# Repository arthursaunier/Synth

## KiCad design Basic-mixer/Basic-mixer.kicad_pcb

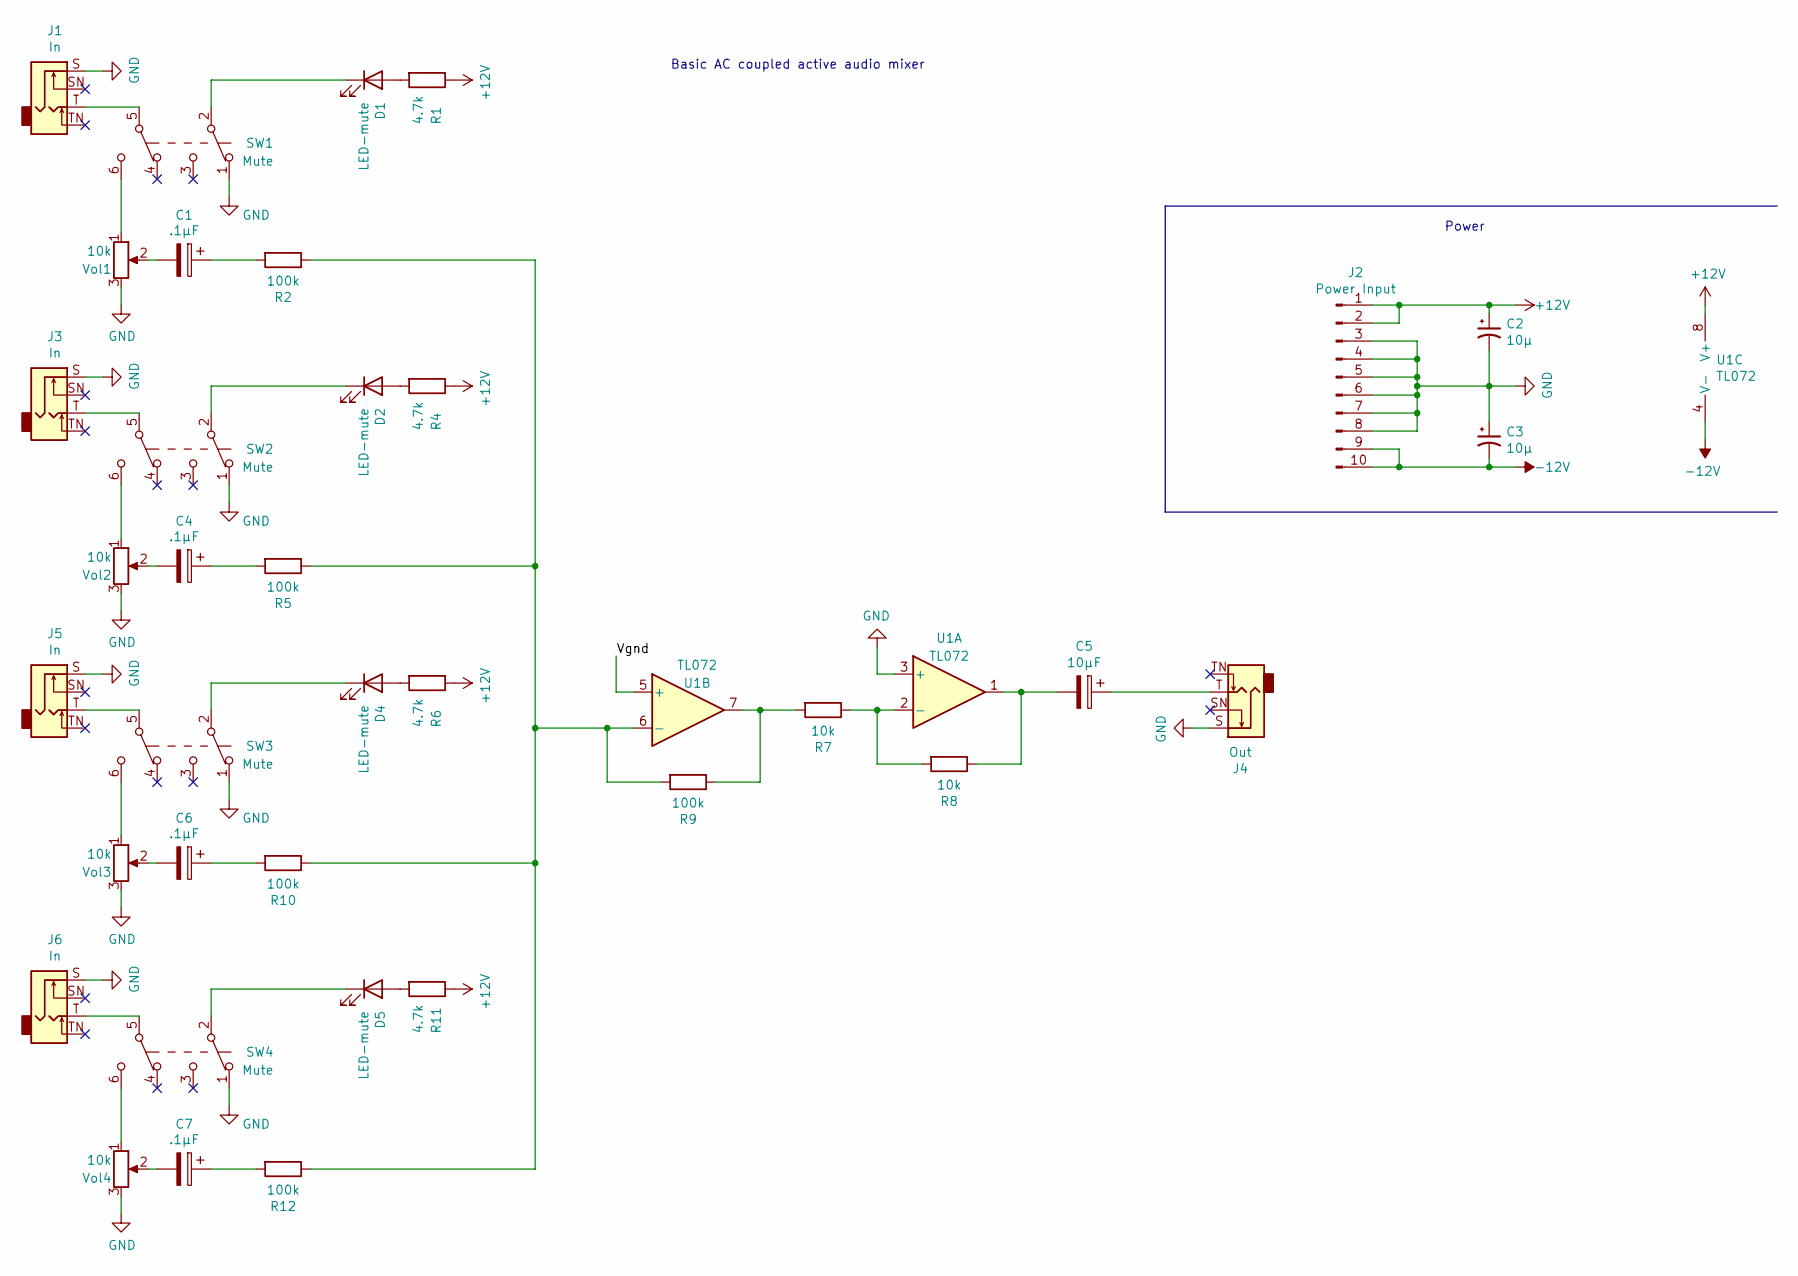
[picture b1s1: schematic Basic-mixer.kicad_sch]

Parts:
C1, C4, C6, C7: .1µF; CP_Radial_D5.0mm_P2.00mm
C2, C3: 10µ; CP_Radial_D5.0mm_P2.00mm
C5: 10µF; CP_Radial_D5.0mm_P2.00mm
D1, D2, D4, D5: LED-mute; LED_D4.0mm
J1, J3, J5, J6: In; Thonkiconn
J2: Power Input; PinHeader_2x05_P2.54mm_Vertical
J4: Out; Thonkiconn
R1, R4, R6, R11: 4.7k; R_Axial_DIN0207_L6.3mm_D2.5mm_P10.16mm_Horizontal
R2, R5, R9, R10, R12: 100k; R_Axial_DIN0207_L6.3mm_D2.5mm_P10.16mm_Horizontal
R7, R8: 10k; R_Axial_DIN0207_L6.3mm_D2.5mm_P10.16mm_Horizontal
SW1, SW2, SW3, SW4: Mute; SW_DPDT_Toggle
U1: TL072; DIP-8_W7.62mm_Socket
Vol1, Vol2, Vol3, Vol4: 10k; Pot-bourns-alpha

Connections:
+12V: C2.1, J2.1, J2.2, R1.1, R4.1, R6.1, R11.1, U1.8 (V+)
-12V: C3.2, J2.9, J2.10, U1.4 (V-)
/Vgnd: U1.5 (+)
GND: C2.2, C3.1, J1.S, J2.3, J2.4, J2.5, J2.6, J2.7, J2.8, J3.S, J4.S, J5.S, J6.S, SW1.1 (A), SW2.1 (A), SW3.1 (A), SW4.1 (A), U1.3 (+), Vol1.3, Vol2.3, Vol3.3, Vol4.3
unnamed: C1.1, R2.2
unnamed: C1.2, Vol1.2
unnamed: C4.1, R5.2
unnamed: C4.2, Vol2.2
unnamed: C5.1, J4.T
unnamed: C5.2, R8.1, U1.1
unnamed: C6.1, R10.2
unnamed: C6.2, Vol3.2
unnamed: C7.1, R12.2
unnamed: C7.2, Vol4.2
unnamed: D1.1 (K), SW1.2 (B)
unnamed: D1.2 (A), R1.2
unnamed: D2.1 (K), SW2.2 (B)
unnamed: D2.2 (A), R4.2
unnamed: D4.1 (K), SW3.2 (B)
unnamed: D4.2 (A), R6.2
unnamed: D5.1 (K), SW4.2 (B)
unnamed: D5.2 (A), R11.2
unnamed: J1.T, SW1.5 (B)
unnamed: J3.T, SW2.5 (B)
unnamed: J5.T, SW3.5 (B)
unnamed: J6.T, SW4.5 (B)
unnamed: R7.1, R8.2, U1.2 (-)
unnamed: R7.2, R9.1, U1.7
unnamed: R2.1, R5.1, R9.2, R10.1, R12.1, U1.6 (-)
unnamed: SW1.6 (C), Vol1.1
unnamed: SW2.6 (C), Vol2.1
unnamed: SW3.6 (C), Vol3.1
unnamed: SW4.6 (C), Vol4.1

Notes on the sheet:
Power
Basic AC coupled active audio mixer

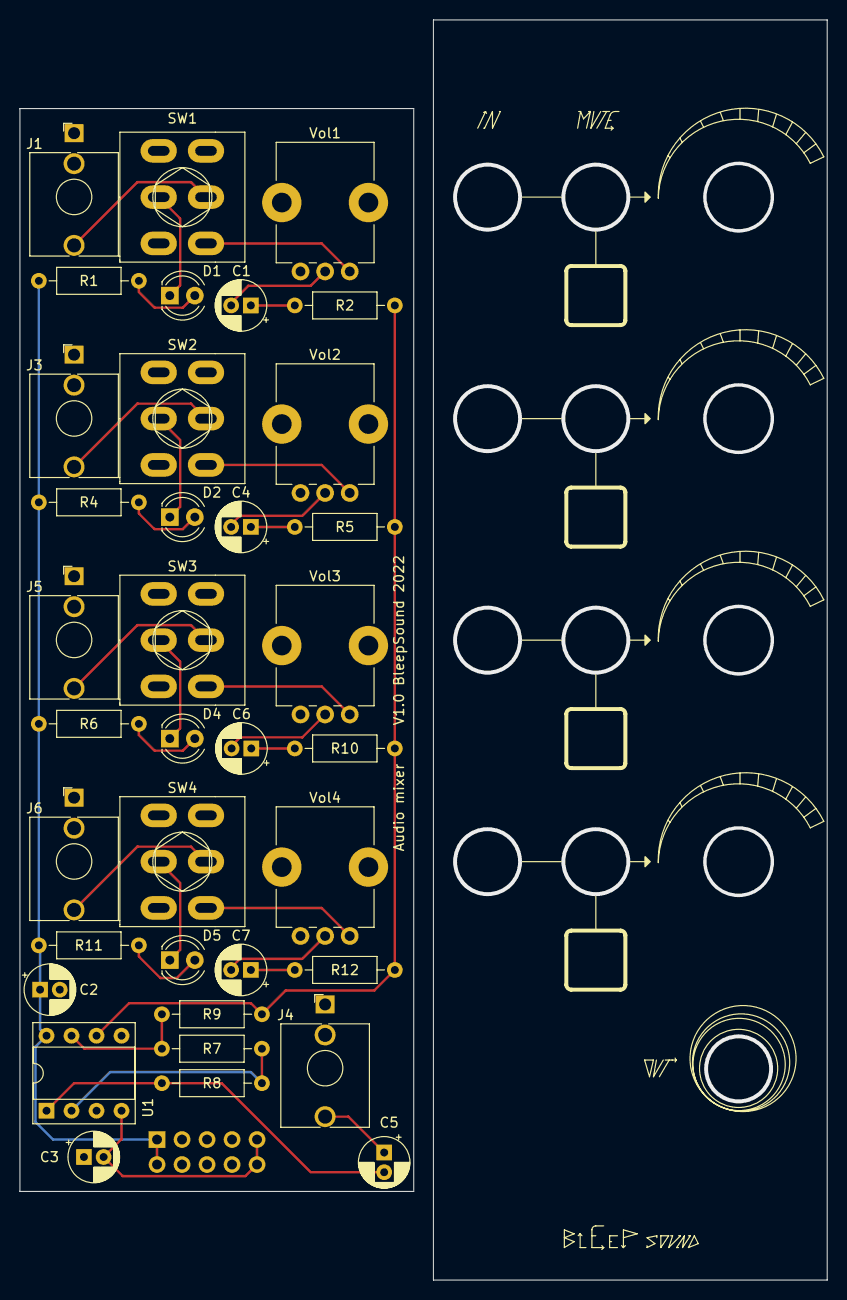
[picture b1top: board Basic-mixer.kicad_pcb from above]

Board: 2 copper layers, 82.0 x 128.0 mm, 37 parts (1 on the bottom side), 32 nets.

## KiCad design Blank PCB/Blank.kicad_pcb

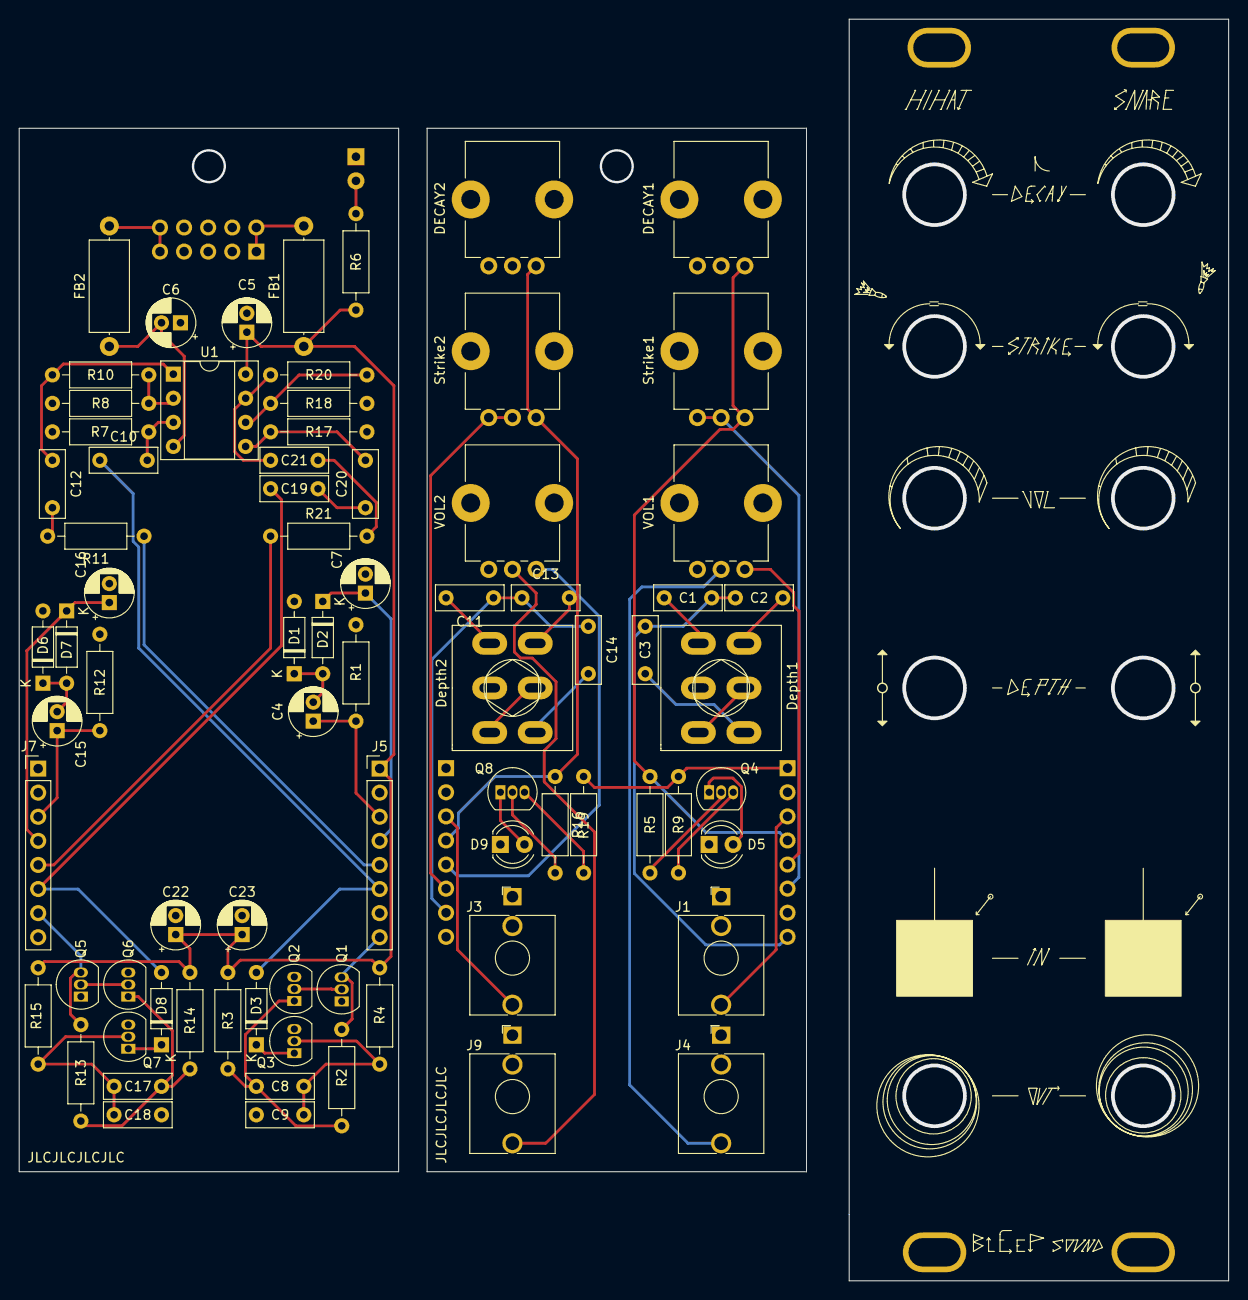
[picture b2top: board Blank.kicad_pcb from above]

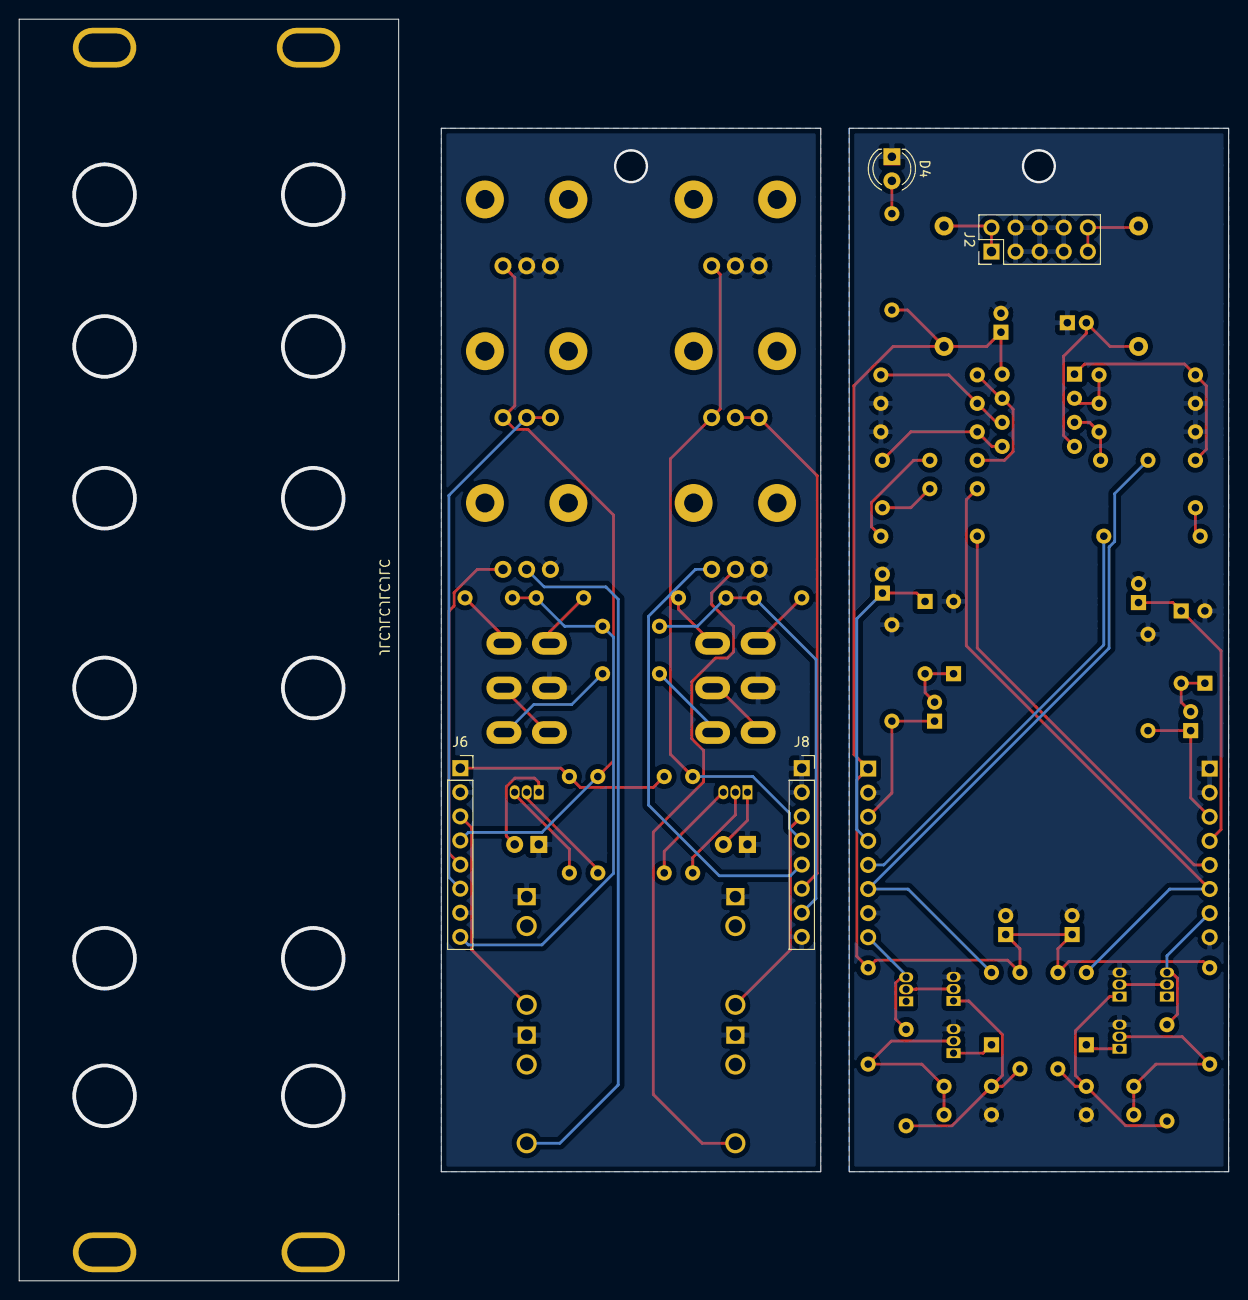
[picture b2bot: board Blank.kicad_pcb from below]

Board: 2 copper layers, 127.5 x 133.0 mm, 81 parts (4 on the bottom side), 51 nets.

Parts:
C1, C11, C12, C21: 10µF; C_Disc_D7.0mm_W2.5mm_P5.00mm
C2, C8, C13, C17: 1µF; C_Disc_D7.0mm_W2.5mm_P5.00mm
C3, C9, C14: 0.1µF; C_Disc_D7.0mm_W2.5mm_P5.00mm
C4, C7, C15, C16: 10µF; CP_Radial_D5.0mm_P2.00mm
C5, C6: 10µ; CP_Radial_D5.0mm_P2.00mm
C10, C20: .1µF; C_Disc_D7.0mm_W2.5mm_P5.00mm
C18: 10nF; C_Disc_D7.0mm_W2.5mm_P5.00mm
C19: 680pF; C_Disc_D7.0mm_W2.5mm_P5.00mm
C22, C23: 100µ; CP_Radial_D5.0mm_P2.00mm
D1, D2, D3, D6, D7, D8: 1N4148; D_DO-35_SOD27_P7.62mm_Horizontal
D4: LED-12V; LED_D4.0mm
D5: Trig Snare; LED_D4.0mm
D9: Trig_HiHat; LED_D4.0mm
DECAY1, DECAY2: 100k; Potentiometer_Bourns_PTV09A-1_Single_Vertical
Depth1, Depth2: SW_Push_DPDT; SW_DPDT_Toggle
FB1, FB2: 10R; L_Axial_L9.5mm_D4.0mm_P12.70mm_Horizontal_Fastron_SMCC
J1: Snare IN; Jack_3.5mm_QingPu_WQP-PJ398SM_Vertical_CircularHoles
J2: Power Input; PinHeader_2x05_P2.54mm_Vertical
J3: HiHat IN; Jack_3.5mm_QingPu_WQP-PJ398SM_Vertical_CircularHoles
J4: Snare OUT; Jack_3.5mm_QingPu_WQP-PJ398SM_Vertical_CircularHoles
J5, J7: Conn_01x08_Male; PinHeader_1x08_P2.54mm_Vertical
J6, J8: Conn_01x08_Female; PinSocket_1x08_P2.54mm_Vertical
J9: HiHat OUT; Jack_3.5mm_QingPu_WQP-PJ398SM_Vertical_CircularHoles
Q1, Q2, Q3, Q5, Q6, Q7: BC546; TO-92_Inline
Q4, Q8: 2N3904; TO-92_Inline
R1, R3, R12, R14: 4k7; R_Axial_DIN0207_L6.3mm_D2.5mm_P10.16mm_Horizontal
R2, R13: 47k; R_Axial_DIN0207_L6.3mm_D2.5mm_P10.16mm_Horizontal
R4, R7, R11, R15, R17, R21: 1M; R_Axial_DIN0207_L6.3mm_D2.5mm_P10.16mm_Horizontal
R5, R10, R16, R20: 100k; R_Axial_DIN0207_L6.3mm_D2.5mm_P10.16mm_Horizontal
R6: 2.2k; R_Axial_DIN0207_L6.3mm_D2.5mm_P10.16mm_Horizontal
R8, R18: 6.8k; R_Axial_DIN0207_L6.3mm_D2.5mm_P10.16mm_Horizontal
R9, R19: 1k; R_Axial_DIN0207_L6.3mm_D2.5mm_P10.16mm_Horizontal
Strike1, Strike2: 100k; Potentiometer_Bourns_PTV09A-1_Single_Vertical
U1: TL072; DIP-8_W7.62mm_Socket
VOL1, VOL2: 10k; Potentiometer_Bourns_PTV09A-1_Single_Vertical

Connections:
+12V: C5.1, C22.1, C23.1, FB1.1, J5.1, J6.1, R3.1, R4.1, R6.1, R9.1, R14.1, R15.1, R19.1, U1.8
-12V: C6.2, FB2.1, U1.4
/DeH: C1.1, C2.1, C3.1, J5.8, J6.8, Q1.3, R2.1
/HiDH: C11.1, C13.1, C14.1, J7.7, J8.7, Q5.3, R13.1
/HiH: C16.1, D7.1, DECAY2.1, J7.4, J8.4, R16.1, Strike2.1
/HiI: C15.1, J3.T, J7.3, J8.3, R12.1
/HiO: J7.5, J8.5, R21.1, VOL2.1
/Ho: C19.1, D8.2, J7.6, J8.6, Strike2.2, Strike2.3
/SnH: C7.1, D2.1, DECAY1.1, J5.4, J6.4, R5.1, Strike1.1
/SnI: C4.1, J1.T, J5.3, J6.3, R1.1
/SnO: J5.5, J6.5, R11.1, VOL1.1
/So: C10.1, D3.2, J5.6, J6.6, Strike1.2, Strike1.3
GND: C5.2, C6.1, C7.2, C9.1, C16.2, C18.1, C22.2, C23.2, D1.2, D4.1, D5.1, D6.2, D9.1, DECAY1.2, DECAY1.3, DECAY2.2, DECAY2.3, Depth1.2, Depth2.2, J1.S, J2.3, J2.4, J2.5, J2.6, J2.7, J2.8, J3.S, J4.S, J5.2, J5.7, J6.2, J6.7, J7.1, J7.2, J7.8, J8.1, J8.2, J8.8, J9.S, Q2.3, Q3.3, Q6.3, Q7.3, R1.2, R7.2, R8.2, R12.2, R17.2, R18.2, VOL1.3, VOL2.3
unnamed: C1.2, Depth1.1
unnamed: C2.2, Depth1.4
unnamed: C3.2, Depth1.6
unnamed: C4.2, D1.1, D2.2
unnamed: C8.1, Q2.1, R2.2, R3.2
unnamed: C8.2, C9.2, Q3.2, R4.2
unnamed: C10.2, R7.1, U1.3
unnamed: C11.2, Depth2.1
unnamed: C12.1, R10.1, U1.1
unnamed: C12.2, R11.2
unnamed: C13.2, Depth2.4
unnamed: C14.2, Depth2.6
unnamed: C15.2, D6.1, D7.2
unnamed: C17.1, Q6.1, R13.2, R14.2
unnamed: C17.2, C18.2, Q7.2, R15.2
unnamed: C19.2, C20.1
unnamed: C20.2, R17.1, U1.5
unnamed: C21.1, R20.1, U1.7
unnamed: C21.2, R21.2
unnamed: D3.1, Q3.1
unnamed: D4.2, R6.2
unnamed: D5.2, Q4.1
unnamed: D8.1, Q7.1
unnamed: D9.2, Q8.1
unnamed: Depth1.3, Depth1.5
unnamed: Depth2.3, Depth2.5
unnamed: FB1.2, J2.1, J2.2
unnamed: FB2.2, J2.9, J2.10
unnamed: J4.T, VOL1.2
unnamed: J9.T, VOL2.2
unnamed: Q1.2, Q2.2
unnamed: Q4.2, R5.2
unnamed: Q4.3, R9.2
unnamed: Q5.2, Q6.2
unnamed: Q8.2, R16.2
unnamed: Q8.3, R19.2
unnamed: R8.1, R10.2, U1.2
unnamed: R18.1, R20.2, U1.6

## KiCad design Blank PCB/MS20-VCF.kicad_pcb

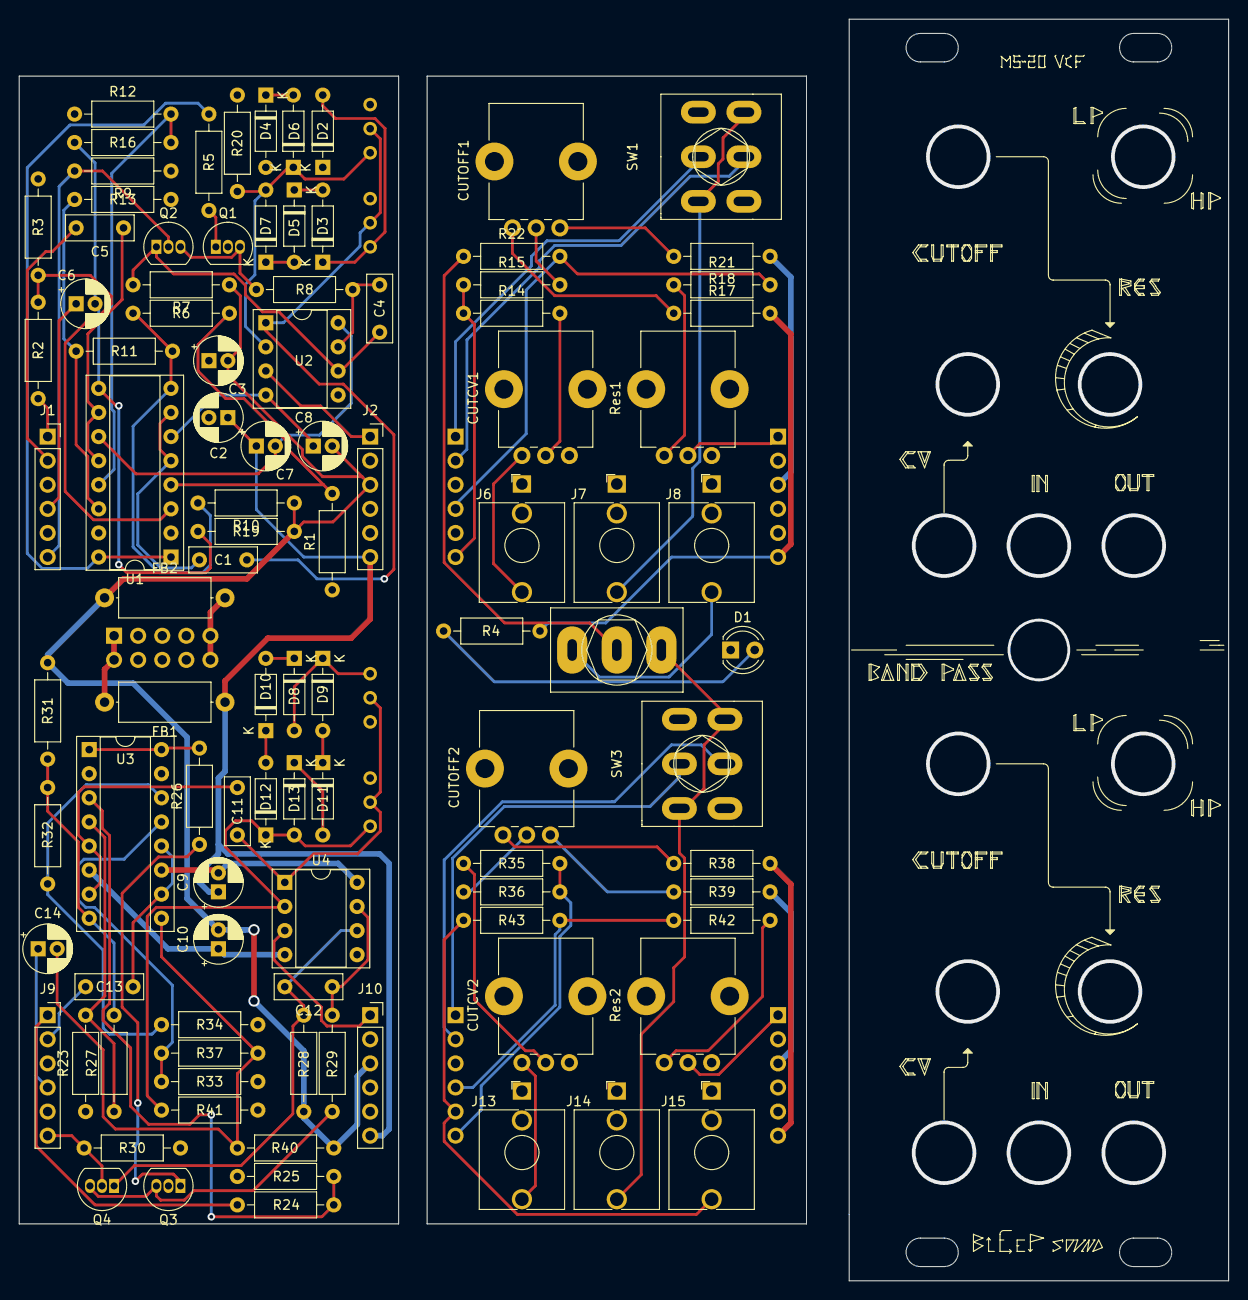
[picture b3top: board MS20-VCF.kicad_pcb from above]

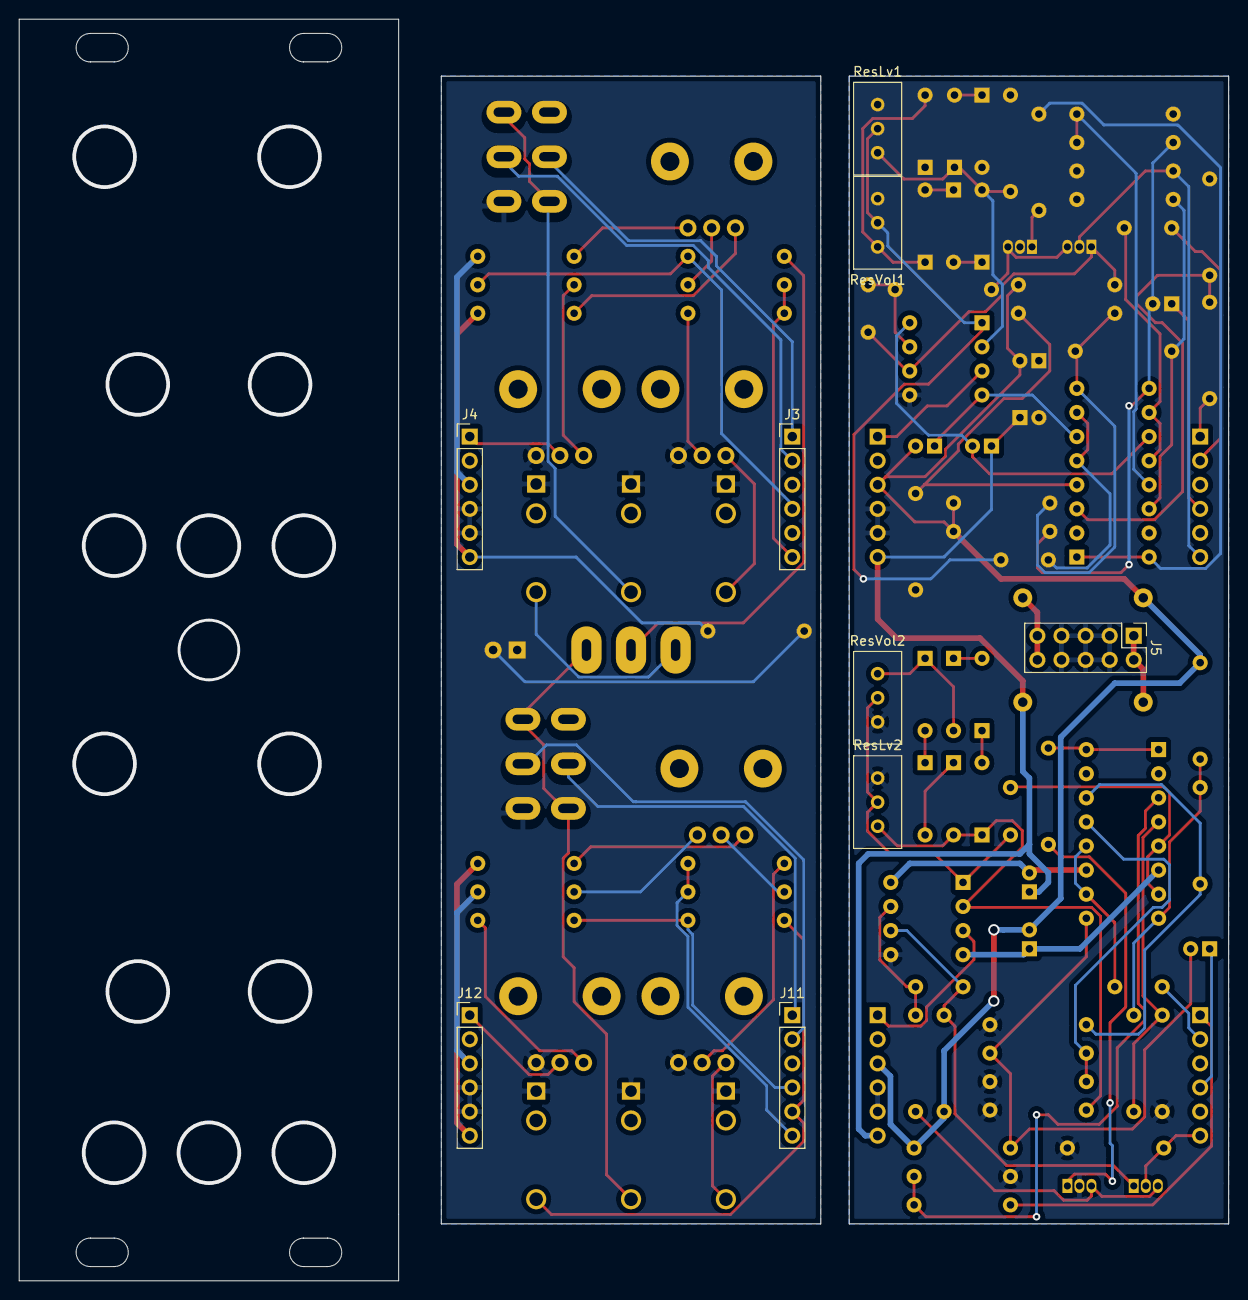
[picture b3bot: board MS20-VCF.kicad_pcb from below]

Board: 2 copper layers, 127.5 x 133.0 mm, 108 parts (9 on the bottom side), 77 nets.

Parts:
C1, C4, C5, C11, C12, C13: 1nF; C_Disc_D7.0mm_W2.5mm_P5.00mm
C2, C3: 10µ; CP_Radial_D5.0mm_P2.00mm
C6, C14: 10µF; CP_Radial_D5.0mm_P2.00mm
C7, C8, C9, C10: 0.1µ; CP_Radial_D5.0mm_P2.00mm
CUTCV1, CUTCV2: 100k; Potentiometer_Bourns_PTV09A-1_Single_Vertical
CUTOFF1, CUTOFF2: 100k; Potentiometer_Bourns_PTV09A-1_Single_Vertical
D1: LED-12V; LED_D4.0mm
D2, D3, D4, D5, D6, D7, D8, D9, D10, D11, D12, D13: 1N4148; D_DO-35_SOD27_P7.62mm_Horizontal
FB1, FB2: 10R; L_Axial_L9.5mm_D4.0mm_P12.70mm_Horizontal_Fastron_SMCC
J1, J2, J9, J10: Conn_CircuitBoard; PinSocket_1x06_P2.54mm_Vertical
J3, J4, J11, J12: Conn_JackBoard; PinHeader_1x06_P2.54mm_Vertical
J5: Power Input; PinHeader_2x05_P2.54mm_Vertical
J6: FilterCV1; Jack_3.5mm_QingPu_WQP-PJ398SM_Vertical_CircularHoles
J7: FilterIn1; Jack_3.5mm_QingPu_WQP-PJ398SM_Vertical_CircularHoles
J8: FilterOut1; Jack_3.5mm_QingPu_WQP-PJ398SM_Vertical_CircularHoles
J13: FilterCV2; Jack_3.5mm_QingPu_WQP-PJ398SM_Vertical_CircularHoles
J14: FilterIn2; Jack_3.5mm_QingPu_WQP-PJ398SM_Vertical_CircularHoles
J15: FilterOut2; Jack_3.5mm_QingPu_WQP-PJ398SM_Vertical_CircularHoles
Q1, Q2, Q3, Q4: BC559; TO-92_Inline
R1, R3, R12, R13, R23, R25, R33, R34: 470; R_Axial_DIN0207_L6.3mm_D2.5mm_P10.16mm_Horizontal
R2, R6, R7, R11, R15, R16, R24, R27, R28, R32, R36, R37: 100k; R_Axial_DIN0207_L6.3mm_D2.5mm_P10.16mm_Horizontal
R4, R5, R9, R20, R26, R30, R41: 2.2k; R_Axial_DIN0207_L6.3mm_D2.5mm_P10.16mm_Horizontal
R8, R21, R22, R29, R42, R43: 1k; R_Axial_DIN0207_L6.3mm_D2.5mm_P10.16mm_Horizontal
R10, R19, R31, R40: 1.8k; R_Axial_DIN0207_L6.3mm_D2.5mm_P10.16mm_Horizontal
R14, R35: 82k; R_Axial_DIN0207_L6.3mm_D2.5mm_P10.16mm_Horizontal
R17, R38: 33k; R_Axial_DIN0207_L6.3mm_D2.5mm_P10.16mm_Horizontal
R18, R39: 56k; R_Axial_DIN0207_L6.3mm_D2.5mm_P10.16mm_Horizontal
Res1, Res2: 100k; Potentiometer_Bourns_PTV09A-1_Single_Vertical
ResLv1, ResLv2: 3.3k; Potentiometer_Bourns_3386C_Horizontal
ResVol1, ResVol2: 10k; Potentiometer_Bourns_3386C_Horizontal
SW1, SW3: Hpass/Lpass Switch; SW_DPDT_Toggle
SW2: Bandpass; SW_Toggle_Blue_wSlots
U1, U3: LM13700; DIP-16_W7.62mm_Socket
U2, U4: TL072; DIP-8_W7.62mm_Socket

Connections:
+12V: C2.1, C7.1, C9.1, FB1.1, J2.6, J4.6, J10.6, J12.6, R4.1, R17.2, R38.2
-12V: C3.2, C8.2, C10.2, FB2.1, J2.3, J4.3, J10.3, J12.3, R7.1, R10.1, R18.1, R19.1, R28.1, R31.1, R39.1, R40.1
/CVIn: CUTCV1.3, J6.T
/Cutoff: J1.6, J3.6, Q2.2, R9.2, R14.1, R15.1
/FilterIn: J7.T, SW1.3, SW1.4
/FilterOut: R22.1, SW2.2
/Filtre2/CVIn: CUTCV2.3, J13.T
/Filtre2/Cutoff: J9.6, J11.6, Q4.2, R30.2, R35.1, R36.1
/Filtre2/FilterOut: J9.5, J11.5, J15.T, R43.1
/Filtre2/HPass: C13.2, J9.2, J11.2, SW3.5
/Filtre2/LPass: J9.1, J11.1, R24.1, SW3.2
/Filtre2/Out1: C14.1, J9.4, J11.4, R42.2, R43.2
/Filtre2/ResOut: J10.1, J12.1, Res2.2, U4.3
/HPass: C5.2, J1.2, J3.2, SW1.5
/JackOut: J8.T, SW2.1
/LPass: J1.1, J3.1, R2.1, SW1.2
/Out1: C6.1, J1.4, J3.4, R21.2, R22.2
/ResOut: J2.1, J4.1, Res1.2, U2.3
Filter2In: J14.T, SW2.3, SW3.3, SW3.4
GND: C2.2, C3.1, CUTCV1.1, CUTCV2.1, D1.1, J2.4, J2.5, J4.4, J4.5, J5.3, J5.4, J5.5, J5.6, J5.7, J5.8, J6.S, J7.S, J8.S, J10.4, J10.5, J12.4, J12.5, J13.S, J14.S, J15.S, Q1.2, Q3.2, R1.1, R3.1, R9.1, R12.1, R13.1, R20.1, R23.1, R25.1, R30.1, R33.1, R34.1, R41.1, Res1.1, Res2.1, ResLv1.1, ResLv2.1, ResVol1.3, ResVol2.3, SW1.6, SW3.6, U2.5, U4.5
unnamed: C1.1, U1.5, U1.7
unnamed: C1.2, ResLv1.2, ResVol1.2, U2.1
unnamed: C4.1, R8.2, U2.7
unnamed: C4.2, Q2.1, R7.2, U2.6
unnamed: C5.1, U1.10, U1.12
unnamed: C6.2, R16.2, R19.2, U1.9
unnamed: C7.2, U1.11, U2.8
unnamed: C8.1, U1.6, U2.4
unnamed: C9.2, U3.11, U4.8
unnamed: C10.1, U3.6, U4.4
unnamed: C11.1, U3.5, U3.7
unnamed: C11.2, ResLv2.2, ResVol2.2, U4.1
unnamed: C12.1, R29.2, U4.7
unnamed: C12.2, Q4.1, R28.2, U4.6
unnamed: C13.1, U3.10, U3.12
unnamed: C14.2, R37.2, R40.2, U3.9
unnamed: CUTCV1.2, R14.2
unnamed: CUTCV2.2, R35.2
unnamed: CUTOFF1.1, R18.2
unnamed: CUTOFF1.2, R15.2
unnamed: CUTOFF1.3, R17.1
unnamed: CUTOFF2.1, R39.2
unnamed: CUTOFF2.2, R36.2
unnamed: CUTOFF2.3, R38.1
unnamed: D1.2, R4.2
unnamed: D2.1, D4.2
unnamed: D2.2, D3.1, ResVol1.1
unnamed: D3.2, D5.1
unnamed: D4.1, D6.2
unnamed: D5.2, D7.1
unnamed: D6.1, D7.2, R20.2, ResLv1.3, U2.2
unnamed: D8.2, D9.1, ResVol2.1
unnamed: D10.1, D12.2
unnamed: D8.1, D10.2
unnamed: D9.2, D11.1
unnamed: D11.2, D13.1
unnamed: D12.1, D13.2, R41.2, ResLv2.3, U4.2
unnamed: FB1.2, J5.1, J5.2
unnamed: FB2.2, J5.9, J5.10
unnamed: Q1.1, R5.1
unnamed: Q1.3, Q2.3, R8.1
unnamed: Q3.1, R26.1
unnamed: Q3.3, Q4.3, R29.1
unnamed: R1.2, R6.1, U1.4
unnamed: R2.2, R3.2, U1.3
unnamed: R5.2, U1.1, U1.16
unnamed: R6.2, R10.2, R11.1, U1.8
unnamed: R11.2, R13.2, U1.14
unnamed: R12.2, R16.1, U1.13
unnamed: R21.1, Res1.3
unnamed: R23.2, R27.1, U3.4
unnamed: R24.2, R25.2, U3.3
unnamed: R26.2, U3.1, U3.16
unnamed: R27.2, R31.2, R32.1, U3.8
unnamed: R32.2, R34.2, U3.14
unnamed: R33.2, R37.1, U3.13
unnamed: R42.1, Res2.3

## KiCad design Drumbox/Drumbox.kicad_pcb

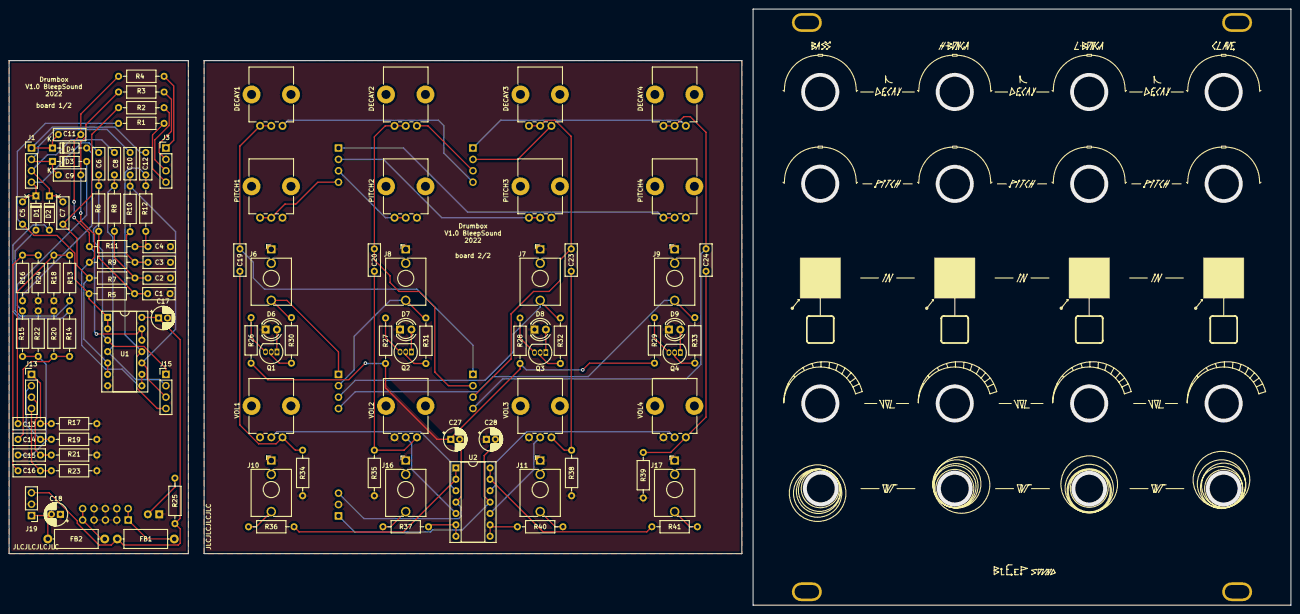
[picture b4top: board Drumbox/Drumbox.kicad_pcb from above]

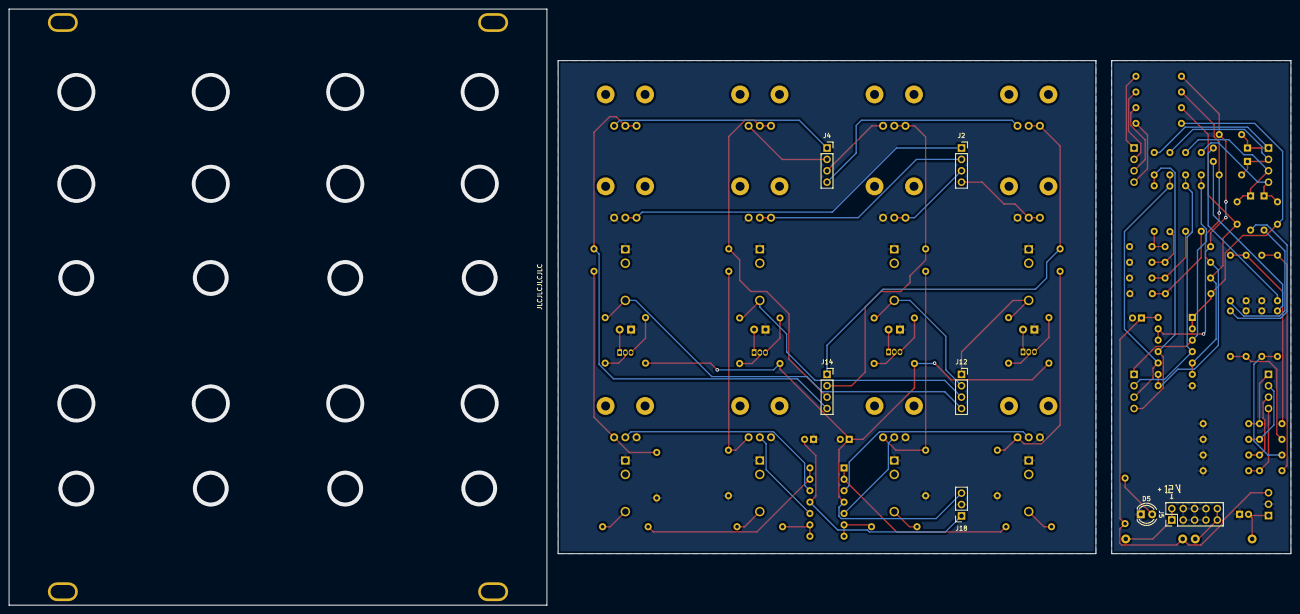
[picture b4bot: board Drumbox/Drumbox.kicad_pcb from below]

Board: 2 copper layers, 286.0 x 133.0 mm, 113 parts (7 on the bottom side), 66 nets.

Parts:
C1, C13: 150nF; C_Disc_D7.0mm_W2.5mm_P5.00mm
C2, C14: 33nF; C_Disc_D7.0mm_W2.5mm_P5.00mm
C3, C15: 39nF; C_Disc_D7.0mm_W2.5mm_P5.00mm
C4: 56nF; C_Disc_D7.0mm_W2.5mm_P5.00mm
C5, C6: 47nF; C_Disc_D7.0mm_W2.5mm_P5.00mm
C7, C8: 10nF; C_Disc_D7.0mm_W2.5mm_P5.00mm
C9, C10: 12nF; C_Disc_D7.0mm_W2.5mm_P5.00mm
C11, C12: 1.5nF; C_Disc_D7.0mm_W2.5mm_P5.00mm
C16: 4.7nF; C_Disc_D7.0mm_W2.5mm_P5.00mm
C17, C18: 10µ; CP_Radial_D5.0mm_P2.00mm
C19, C20, C23, C24: .1µF; C_Disc_D7.0mm_W2.5mm_P5.00mm
C27, C28: 100n; CP_Radial_D5.0mm_P2.00mm
D1, D2, D3, D4: 1N4148; D_DO-35_SOD27_P7.62mm_Horizontal
D5: LED-12V; LED_D4.0mm
D6: LED1; LED_D4.0mm
D7: LED2; LED_D4.0mm
D8: LED3; LED_D4.0mm
D9: LED4; LED_D4.0mm
DECAY1, DECAY2, DECAY3, DECAY4: 470k; Potentiometer_Bourns_PTV09A-1_Single_Vertical
FB1, FB2: 10R; L_Axial_L9.5mm_D4.0mm_P12.70mm_Horizontal_Fastron_SMCC
J1, J3, J13, J15: Conn_01x04_Male; PinHeader_1x04_P2.54mm_Vertical
J2, J4, J12, J14: Conn_01x04_Female; PinSocket_1x04_P2.54mm_Vertical
J5: Power Input; PinHeader_2x05_P2.54mm_Vertical
J6: Bass IN; Jack_3.5mm_QingPu_WQP-PJ398SM_Vertical_CircularHoles
J7: LBonga IN; Jack_3.5mm_QingPu_WQP-PJ398SM_Vertical_CircularHoles
J8: HBonga IN; Jack_3.5mm_QingPu_WQP-PJ398SM_Vertical_CircularHoles
J9: Clave IN; Jack_3.5mm_QingPu_WQP-PJ398SM_Vertical_CircularHoles
J10: Bass OUT; Jack_3.5mm_QingPu_WQP-PJ398SM_Vertical_CircularHoles
J11: LBonga OUT; Jack_3.5mm_QingPu_WQP-PJ398SM_Vertical_CircularHoles
J16: HBonga OUT; Jack_3.5mm_QingPu_WQP-PJ398SM_Vertical_CircularHoles
J17: Clave OUT; Jack_3.5mm_QingPu_WQP-PJ398SM_Vertical_CircularHoles
J18: Conn_01x03_Female; PinSocket_1x03_P2.54mm_Vertical
J19: Conn_01x03_Male; PinHeader_1x03_P2.54mm_Vertical
PITCH1, PITCH2, PITCH3, PITCH4: 10k; Potentiometer_Bourns_PTV09A-1_Single_Vertical
Q1, Q2, Q3, Q4: 2N3904; TO-92_Inline
R1, R2, R3, R4: 150k; R_Axial_DIN0207_L6.3mm_D2.5mm_P10.16mm_Horizontal
R5, R6, R7, R8, R9, R10, R11, R12: 68k; R_Axial_DIN0207_L6.3mm_D2.5mm_P10.16mm_Horizontal
R13, R14, R15, R16: 27k; R_Axial_DIN0207_L6.3mm_D2.5mm_P10.16mm_Horizontal
R17, R19, R21, R23: 12k; R_Axial_DIN0207_L6.3mm_D2.5mm_P10.16mm_Horizontal
R18, R20, R22, R24, R30, R31, R32, R33: 47k; R_Axial_DIN0207_L6.3mm_D2.5mm_P10.16mm_Horizontal
R25: 2.2k; R_Axial_DIN0207_L6.3mm_D2.5mm_P10.16mm_Horizontal
R26, R27, R28, R29, R36, R37, R40, R41: 1k; R_Axial_DIN0207_L6.3mm_D2.5mm_P10.16mm_Horizontal
R34, R35, R38, R39: 1M; R_Axial_DIN0207_L6.3mm_D2.5mm_P10.16mm_Horizontal
U1: 4011; DIP-14_W7.62mm_Socket
U2: TL074; DIP-14_W7.62mm_Socket
VOL1, VOL2, VOL3, VOL4: 10k; Potentiometer_Bourns_PTV09A-1_Single_Vertical

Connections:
+12V: C17.1, C27.1, FB1.1, J18.3, J19.3, R25.1, R26.1, R27.1, R28.1, R29.1, U1.14 (VDD), U2.4 (V+)
-12V: C18.2, C28.2, FB2.1, J18.1, J19.1, U2.11 (V-)
DEIn1: DECAY1.1, J3.4, J4.4, R1.1
DEIn2: DECAY2.1, J3.3, J4.3, R2.1
DEIn3: DECAY3.1, J3.2, J4.2, R3.1
DEIn4: DECAY4.1, J3.1, J4.1, R4.1
GND: C1.2, C2.2, C3.2, C4.2, C17.2, C18.1, C27.2, C28.1, D5.1 (K), D6.1 (K), D7.1 (K), D8.1 (K), D9.1 (K), J5.3, J5.4, J5.5, J5.6, J5.7, J5.8, J6.S, J7.S, J8.S, J9.S, J10.S, J11.S, J16.S, J17.S, J18.2, J19.2, PITCH1.1, PITCH2.1, PITCH3.1, PITCH4.1, R17.2, R18.1, R19.2, R20.1, R21.2, R22.1, R23.2, R24.1, R34.2, R35.2, R38.2, R39.2, U1.7 (VSS), VOL1.3, VOL2.3, VOL3.3, VOL4.3
In1: C13.1, J6.T, J12.1, J13.1, R17.1, R30.1
In2: C14.1, J8.T, J12.2, J13.2, R19.1, R31.1
In3: C15.1, J7.T, J12.3, J13.3, R21.1, R32.1
In4: C16.1, J9.T, J12.4, J13.4, R23.1, R33.1
unnamed: C1.1, R5.1, R6.2
unnamed: C2.1, R7.1, R8.2
unnamed: C3.1, R9.1, R10.2
unnamed: C4.1, R11.1, R12.2
unnamed: C5.1, R1.2, R5.2, U1.1, U1.2
unnamed: C7.1, R2.2, R7.2, U1.5, U1.6
unnamed: C9.1, R3.2, R9.2, U1.8, U1.9
unnamed: C11.1, R4.2, R11.2, U1.12, U1.13
unnamed: C13.2, R13.1, R18.2
unnamed: C14.2, R14.1, R20.2
unnamed: C15.2, R15.1, R22.2
unnamed: C16.2, R16.1, R24.2
unnamed: C19.2, R34.1, VOL1.1
unnamed: C20.2, R35.1, VOL2.1
unnamed: C23.2, R38.1, VOL3.1
unnamed: C24.2, R39.1, VOL4.1
unnamed: D1.2 (A), R13.2
unnamed: D2.2 (A), R14.2
unnamed: D3.2 (A), R15.2
unnamed: D4.2 (A), R16.2
unnamed: D5.2 (A), R25.2
unnamed: D6.2 (A), Q1.1 (E)
unnamed: D7.2 (A), Q2.1 (E)
unnamed: D8.2 (A), Q3.1 (E)
unnamed: D9.2 (A), Q4.1 (E)
unnamed: FB1.2, J5.1, J5.2
unnamed: FB2.2, J5.9, J5.10
unnamed: Q1.2 (B), R30.2
unnamed: Q1.3 (C), R26.2
unnamed: Q2.2 (B), R31.2
unnamed: Q2.3 (C), R27.2
unnamed: Q3.2 (B), R32.2
unnamed: Q3.3 (C), R28.2
unnamed: Q4.2 (B), R33.2
unnamed: Q4.3 (C), R29.2
unnamed: R36.2, U2.1, U2.2 (-)
unnamed: R37.2, U2.6 (-), U2.7
unnamed: R40.2, U2.8, U2.9 (-)
unnamed: R41.2, U2.13 (-), U2.14
unnamed: U2.3 (+), VOL1.2
unnamed: U2.5 (+), VOL2.2
unnamed: U2.10 (+), VOL3.2
unnamed: U2.12 (+), VOL4.2
O1: C6.2, C19.1, DECAY1.2, DECAY1.3, J14.1, J15.1, R6.1, U1.3
O2: C8.2, C20.1, DECAY2.2, DECAY2.3, J14.2, J15.2, R8.1, U1.4
O3: C10.2, C23.1, DECAY3.2, DECAY3.3, J14.3, J15.3, R10.1, U1.10
O4: C12.2, C24.1, DECAY4.2, DECAY4.3, J14.4, J15.4, R12.1, U1.11
Out1: J10.T, R36.1
Out2: J16.T, R37.1
Out3: J11.T, R40.1
Out4: J17.T, R41.1
PIOut1: C5.2, C6.1, D1.1 (K), J1.4, J2.4, PITCH1.2, PITCH1.3
PIOut2: C7.2, C8.1, D2.1 (K), J1.3, J2.3, PITCH2.2, PITCH2.3
PIOut3: C9.2, C10.1, D3.1 (K), J1.2, J2.2, PITCH3.2, PITCH3.3
PIOut4: C11.2, C12.1, D4.1 (K), J1.1, J2.1, PITCH4.2, PITCH4.3
